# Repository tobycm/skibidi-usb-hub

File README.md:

# skibidi usb hub - 7-port usb hub with some ethernet and an audio out jack

me when my ethernet port and audio jack is broken and i need more usb A ports :bonk:

features:
 - 1 USB C port for upstream
 - 2 USB C ports
 - 2 USB A ports
 - 2 100M capable Ethernet ports
 - 1 Audio Jack (maybe both line in and line out)

## Build

JLCPCB Params:
- Stack up: JLC04161H-7628

## Pictures:

PCB Front: 

PCB Back:

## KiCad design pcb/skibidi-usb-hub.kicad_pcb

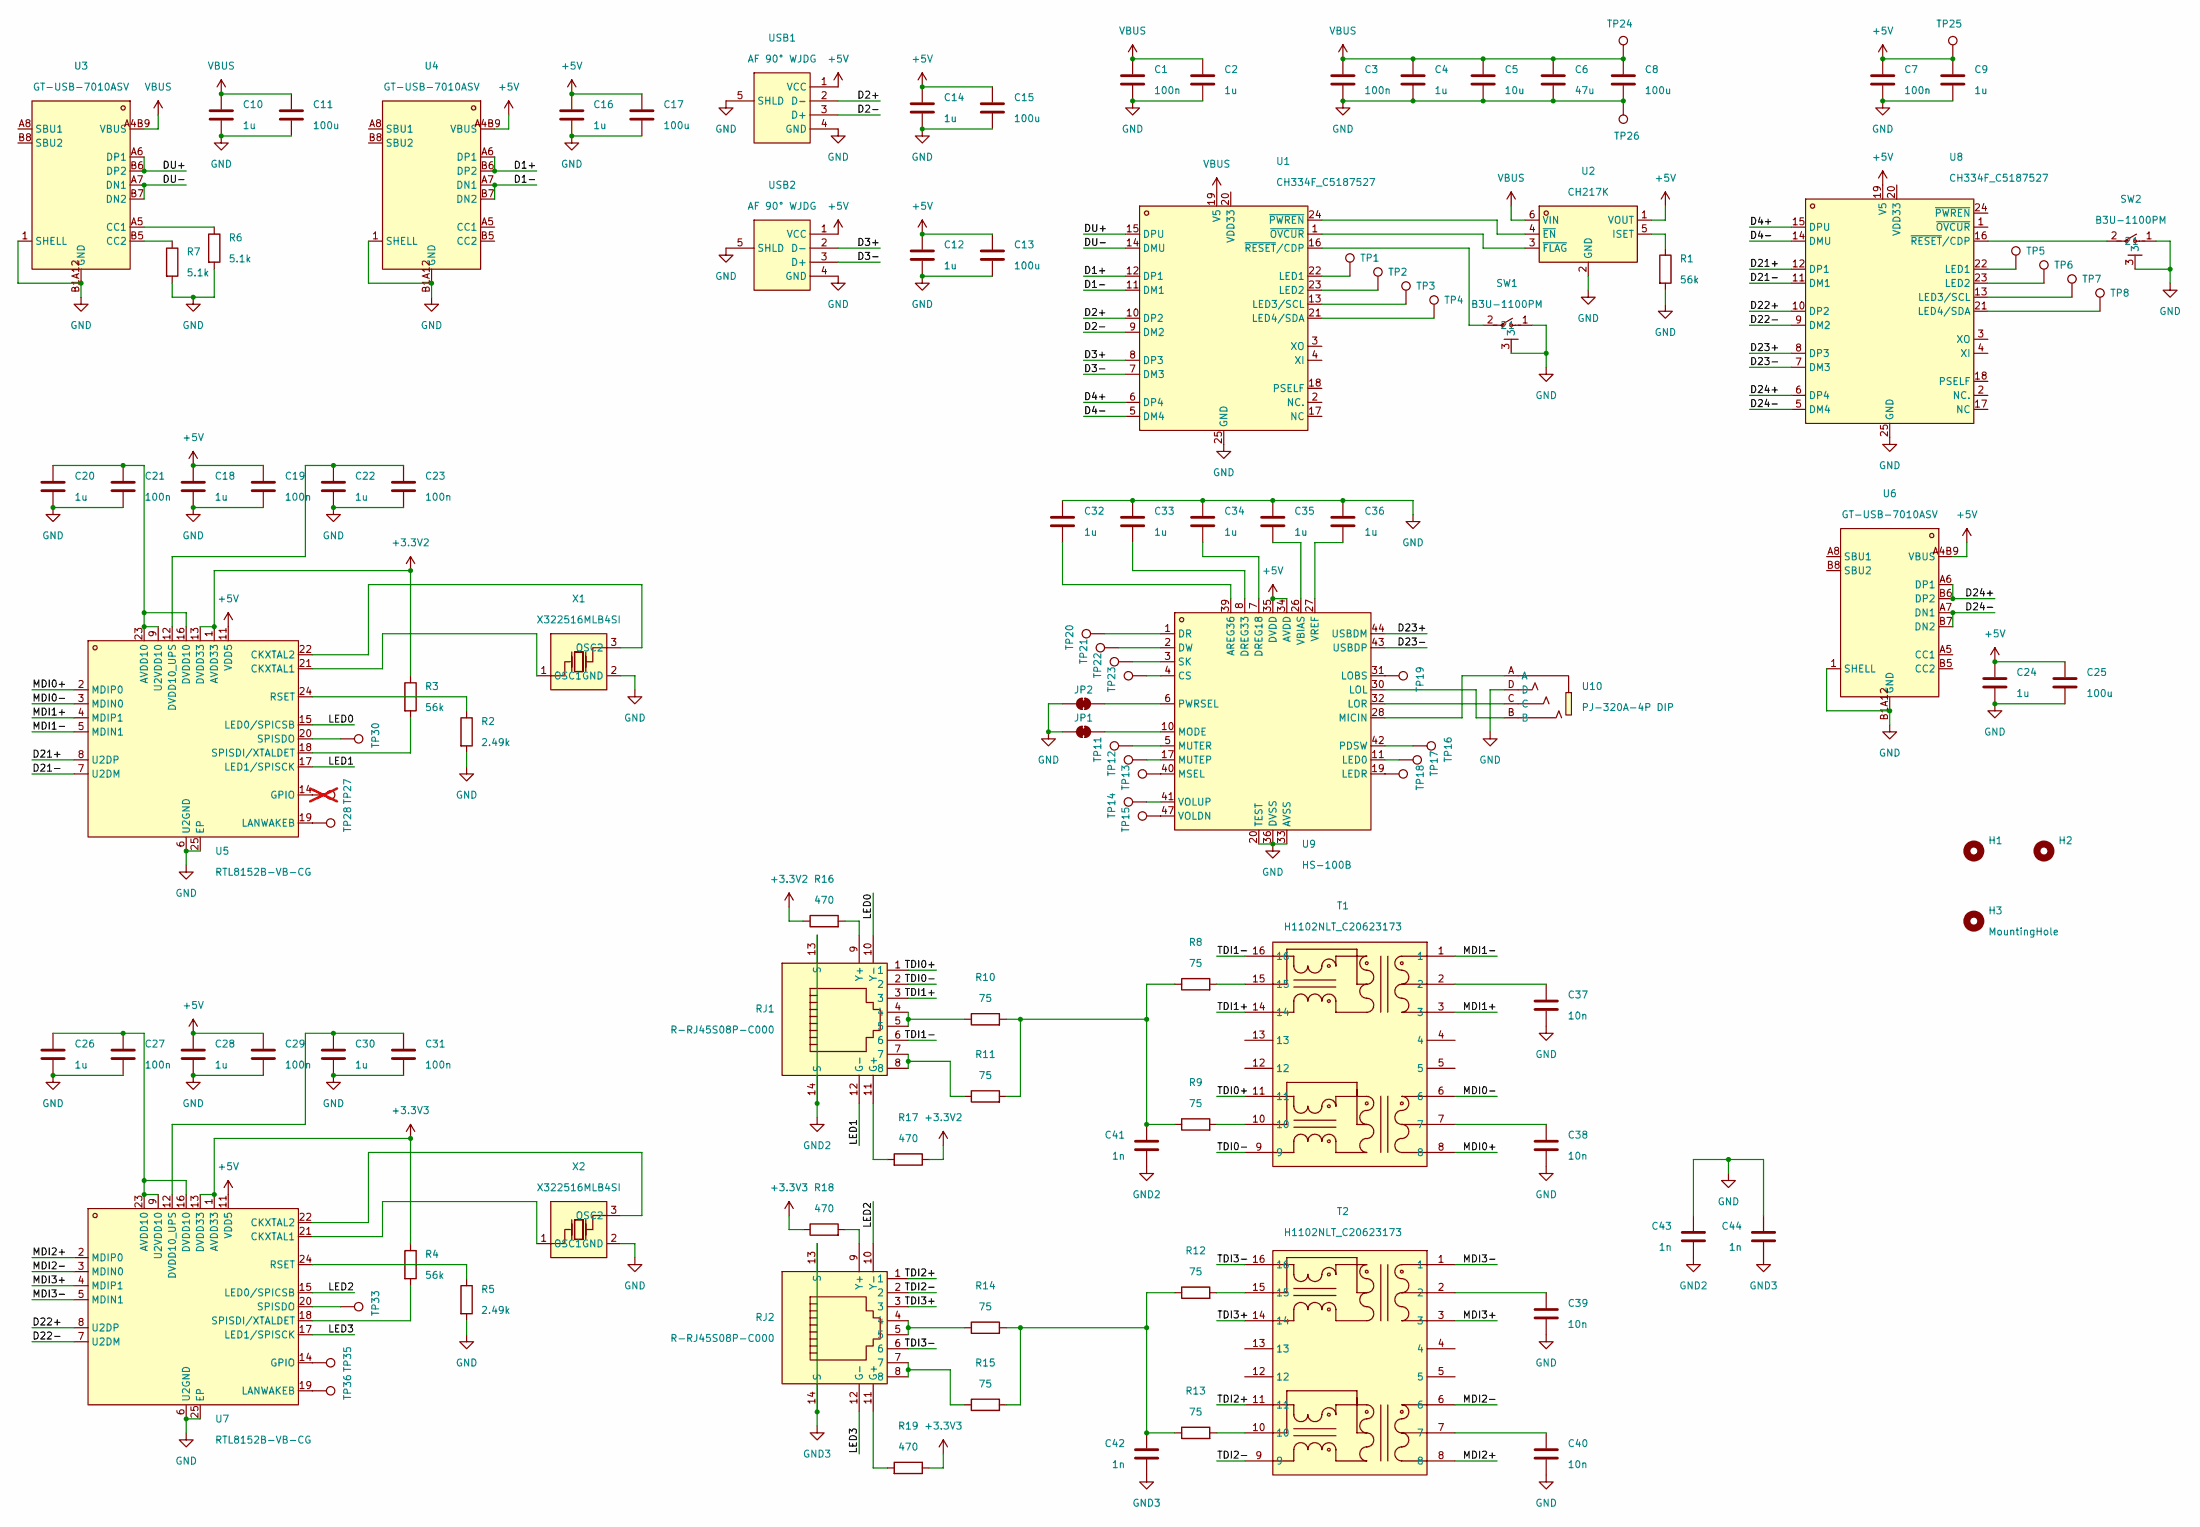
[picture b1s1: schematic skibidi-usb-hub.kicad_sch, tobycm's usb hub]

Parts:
C1, C3, C7, C19, C21, C23, C27, C29, C31: 100n; C_0402_1005Metric; LCSC Part # C1525
C2, C4, C9, C10, C12, C14, C16, C18, C20, C22, C24, C26, C28, C30, C32, C33, C34, C35, C36: 1u; C_0402_1005Metric; LCSC Part # C52923
C5: 10u; C_0603_1608Metric; LCSC Part # C19702
C6: 47u; C_0805_2012Metric; LCSC Part # C16780
C8, C11, C13, C15, C17, C25: 100u; C_1206_3216Metric; LCSC Part # C15008
C37, C38, C39, C40: 10n; C_0402_1005Metric; LCSC Part # C60133
C41, C42, C43, C44: 1n; C_1206_3216Metric; LCSC Part # C9196
H1, H2, H3: MountingHole; MountingHole_3.2mm_M3_Pad
JP1, JP2: SolderJumper_2_Bridged; SolderJumper-2_P1.3mm_Bridged_RoundedPad1.0x1.5mm
R1, R3, R4: 56k; R_0402_1005Metric; LCSC Part # C25796
R2, R5: 2.49k; R_0402_1005Metric; LCSC Part # C25884
R6, R7: 5.1k; R_0402_1005Metric; LCSC Part # C25905
R8, R9, R10, R11, R12, R13, R14, R15: 75; R_0402_1005Metric; LCSC Part # C114757
R16, R17, R18, R19: 470; R_0402_1005Metric; LCSC Part # C114877
RJ1, RJ2: R-RJ45S08P-C000; RJ45-TH_R-RJ45S08P-C000; LCSC Part C386764
SW1, SW2: B3U-1100PM; SW-SMD_3P-L3.0-W2.5-LS4.0; LCSC Part C6467298
T1, T2: H1102NLT_C20623173; XFMR-SMD_H1102NLT; LCSC Part C20623173
TP1, TP2, TP3, TP4, TP5, TP6, TP7, TP8, TP11, TP12, TP13, TP14, TP15, TP16, TP17, TP18, TP19, TP20, TP21, TP22, TP23, TP24, TP25, TP26, TP28, TP30, TP33, TP35, TP36: TestPoint; TestPoint_Pad_D1.0mm
TP27: TestPoint; TestPoint_Pad_D1.0mm; not fitted
U1, U8: CH334F_C5187527; QFN-24_L4.0-W4.0-P0.50-BL-EP2.8; LCSC Part C5187527
U2: CH217K; SOT-23-6_L2.9-W1.6-P0.95-LS2.8-BL; LCSC Part C7462749
U3, U4, U6: GT-USB-7010ASV; USB-C-SMD_G-SWITCH_GT-USB-7010ASV; LCSC Part C2988369
U5, U7: RTL8152B-VB-CG; QFN-24_L4.0-W4.0-P0.50-BL-EP2.0; LCSC Part C50656
U9: HS-100B; LQFP-48_L7.0-W7.0-P0.50-LS9.0-BL; LCSC Part C371351
U10: PJ-320A-4P DIP; AUDIO-TH_PJ-320A-4P-DIP; LCSC Part C18185602
USB1, USB2: AF 90° WJDG; USB-A-TH_AF-WJDG; LCSC Part C456018
X1, X2: X322516MLB4SI; OSC-SMD_4P-L3.2-W2.5-BL; LCSC Part C13738

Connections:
+3.3V2: R3.1, R16.1, R17.1, U5.1 (AVDD33), U5.10 (AVDD33), U5.13 (DVDD33)
+3.3V3: R4.1, R18.1, R19.1, U7.1 (AVDD33), U7.10 (AVDD33), U7.13 (DVDD33)
+5V: C7.1, C9.1, C12.1, C13.1, C14.1, C15.1, C16.1, C17.1, C18.1, C19.1, C24.1, C25.1, C28.1, C29.1, TP25.1, U2.1 (VOUT), U4.A4B9 (VBUS), U4.B4A9 (VBUS), U5.11 (VDD5), U6.A4B9 (VBUS), U6.B4A9 (VBUS), U7.11 (VDD5), U8.19 (V5), U9.29 (AVDD), U9.34 (AVDD), U9.35 (DVDD), USB1.1 (VCC), USB2.1 (VCC)
/D1+: U1.12 (DP1), U4.A6 (DP1), U4.B6 (DP2)
/D1-: U1.11 (DM1), U4.A7 (DN1), U4.B7 (DN2)
/D2+: U1.10 (DP2), USB1.2 (D-)
/D2-: U1.9 (DM2), USB1.3 (D+)
/D3+: U1.8 (DP3), USB2.2 (D-)
/D3-: U1.7 (DM3), USB2.3 (D+)
/D4+: U1.6 (DP4), U8.15 (DPU)
/D4-: U1.5 (DM4), U8.14 (DMU)
/D21+: U5.8 (U2DP), U8.12 (DP1)
/D21-: U5.7 (U2DM), U8.11 (DM1)
/D22+: U7.8 (U2DP), U8.10 (DP2)
/D22-: U7.7 (U2DM), U8.9 (DM2)
/D23+: U8.8 (DP3), U9.44 (USBDM)
/D23-: U8.7 (DM3), U9.43 (USBDP)
/D24+: U6.A6 (DP1), U6.B6 (DP2), U8.6 (DP4)
/D24-: U6.A7 (DN1), U6.B7 (DN2), U8.5 (DM4)
/DU+: U1.15 (DPU), U3.A6 (DP1), U3.B6 (DP2)
/DU-: U1.14 (DMU), U3.A7 (DN1), U3.B7 (DN2)
/LED0: RJ1.10 (Y-), U5.15 (LED0/SPICSB)
/LED1: RJ1.12 (G-), U5.17 (LED1/SPISCK)
/LED2: RJ2.10 (Y-), U7.15 (LED0/SPICSB)
/LED3: RJ2.12 (G-), U7.17 (LED1/SPISCK)
/MDI0+: T1.8, U5.2 (MDIP0)
/MDI0-: T1.6, U5.3 (MDIN0)
/MDI1+: T1.3, U5.4 (MDIP1)
/MDI1-: T1.1, U5.5 (MDIN1)
/MDI2+: T2.8, U7.2 (MDIP0)
/MDI2-: T2.6, U7.3 (MDIN0)
/MDI3+: T2.3, U7.4 (MDIP1)
/MDI3-: T2.1, U7.5 (MDIN1)
/TDI0+: RJ1.1, T1.11
/TDI0-: RJ1.2, T1.9
/TDI1+: RJ1.3, T1.14
/TDI1-: RJ1.6, T1.16
/TDI2+: RJ2.1, T2.11
/TDI2-: RJ2.2, T2.9
/TDI3+: RJ2.3, T2.14
/TDI3-: RJ2.6, T2.16
GND: C1.2, C2.2, C3.2, C4.2, C5.2, C6.2, C7.2, C8.2, C9.2, C10.2, C11.2, C12.2, C13.2, C14.2, C15.2, C16.2, C17.2, C18.2, C19.2, C20.2, C21.2, C22.2, C23.2, C24.2, C25.2, C26.2, C27.2, C28.2, C29.2, C30.2, C31.2, C32.1, C33.1, C34.1, C35.1, C36.1, C37.2, C38.2, C39.2, C40.2, C43.1, C44.1, JP1.1 (A), JP2.1 (A), R1.2, R2.2, R5.2, R6.2, R7.2, SW1.1, SW1.3, SW2.1, SW2.3, TP26.1, U1.25 (GND), U2.2 (GND), U3.1 (SHELL), U3.2 (SHELL), U3.3 (SHELL), U3.4 (SHELL), U3.A1B12 (GND), U3.B1A12 (GND), U4.1 (SHELL), U4.2 (SHELL), U4.3 (SHELL), U4.4 (SHELL), U4.A1B12 (GND), U4.B1A12 (GND), U5.6 (U2GND), U5.25 (EP), U6.1 (SHELL), U6.2 (SHELL), U6.3 (SHELL), U6.4 (SHELL), U6.A1B12 (GND), U6.B1A12 (GND), U7.6 (U2GND), U7.25 (EP), U8.25 (GND), U9.12 (DVSS), U9.20 (TEST), U9.25 (AVSS), U9.33 (AVSS), U9.36 (DVSS), U10.D, USB1.4 (GND), USB1.5 (SHLD), USB2.4 (GND), USB2.5 (SHLD), X1.2 (GND), X1.4 (GND), X2.2 (GND), X2.4 (GND)
GND2: C41.2, C43.2, RJ1.13 (S), RJ1.14 (S)
GND3: C42.2, C44.2, RJ2.13 (S), RJ2.14 (S)
unnamed: C37.1, T1.2
unnamed: C38.1, T1.7
unnamed: C39.1, T2.2
unnamed: C40.1, T2.7
unnamed: C41.1, R8.1, R9.1, R10.2, R11.2
unnamed: C42.1, R12.1, R13.1, R14.2, R15.2
unnamed: JP1.2 (B), U9.10 (MODE)
unnamed: JP2.2 (B), U9.6 (PWRSEL)
unnamed: R8.2, T1.15
unnamed: R9.2, T1.10
unnamed: R10.1, RJ1.4, RJ1.5
unnamed: R11.1, RJ1.7, RJ1.8
unnamed: R12.2, T2.15
unnamed: R13.2, T2.10
unnamed: R14.1, RJ2.4, RJ2.5
unnamed: R15.1, RJ2.7, RJ2.8
unnamed: R17.2, RJ1.11 (G+)
unnamed: R16.2, RJ1.9 (Y+)
unnamed: R19.2, RJ2.11 (G+)
unnamed: R18.2, RJ2.9 (Y+)
unnamed: TP1.1, U1.22 (LED1)
unnamed: TP2.1, U1.23 (LED2)
unnamed: TP3.1, U1.13 (LED3/SCL)
unnamed: TP4.1, U1.21 (LED4/SDA)
unnamed: U1.1 (~OVCUR), U2.3 (~FLAG)
unnamed: U1.24 (~PWREN), U2.4 (~EN)
unnamed: SW1.2, U1.16 (~RESET/CDP)
unnamed: R1.1, U2.5 (ISET)
unnamed: R6.1, U3.A5 (CC1)
unnamed: R7.1, U3.B5 (CC2)
unnamed: C20.1, C21.1, U5.9 (U2VDD10), U5.16 (DVDD10), U5.23 (AVDD10)
unnamed: U5.21 (CKXTAL1), X1.1 (OSC1)
unnamed: U5.22 (CKXTAL2), X1.3 (OSC2)
unnamed: C22.1, C23.1, U5.12 (DVDD10_UPS)
unnamed: TP27.1, U5.14 (GPIO)
unnamed: TP28.1, U5.19 (LANWAKEB)
unnamed: R2.1, U5.24 (RSET)
unnamed: R3.2, U5.18 (SPISDI/XTALDET)
unnamed: TP30.1, U5.20 (SPISDO)
unnamed: C26.1, C27.1, U7.9 (U2VDD10), U7.16 (DVDD10), U7.23 (AVDD10)
unnamed: U7.21 (CKXTAL1), X2.1 (OSC1)
unnamed: U7.22 (CKXTAL2), X2.3 (OSC2)
unnamed: C30.1, C31.1, U7.12 (DVDD10_UPS)
unnamed: TP35.1, U7.14 (GPIO)
unnamed: TP36.1, U7.19 (LANWAKEB)
unnamed: R5.1, U7.24 (RSET)
unnamed: R4.2, U7.18 (SPISDI/XTALDET)
unnamed: TP33.1, U7.20 (SPISDO)
unnamed: TP5.1, U8.22 (LED1)
unnamed: TP6.1, U8.23 (LED2)
unnamed: TP7.1, U8.13 (LED3/SCL)
unnamed: TP8.1, U8.21 (LED4/SDA)
unnamed: SW2.2, U8.16 (~RESET/CDP)
unnamed: C32.2, U9.39 (AREG36)
unnamed: TP23.1, U9.4 (CS)
unnamed: TP20.1, U9.1 (DR)
unnamed: C34.2, U9.7 (DREG18)
unnamed: C33.2, U9.8 (DREG33)
unnamed: TP21.1, U9.2 (DW)
unnamed: TP17.1, U9.11 (LED0)
unnamed: TP18.1, U9.19 (LEDR)
unnamed: TP19.1, U9.31 (LOBS)
unnamed: U9.30 (LOL), U10.B
unnamed: U9.32 (LOR), U10.C
unnamed: U9.28 (MICIN), U10.A
unnamed: TP13.1, U9.40 (MSEL)
unnamed: TP12.1, U9.17 (MUTEP)
unnamed: TP11.1, U9.5 (MUTER)
unnamed: TP16.1, U9.42 (PDSW)
unnamed: TP22.1, U9.3 (SK)
unnamed: C35.2, U9.26 (VBIAS)
unnamed: TP15.1, U9.47 (VOLDN)
unnamed: TP14.1, U9.41 (VOLUP)
unnamed: C36.2, U9.27 (VREF)
VBUS: C1.1, C2.1, C3.1, C4.1, C5.1, C6.1, C8.1, C10.1, C11.1, TP24.1, U1.19 (V5), U2.6 (VIN), U3.A4B9 (VBUS), U3.B4A9 (VBUS)

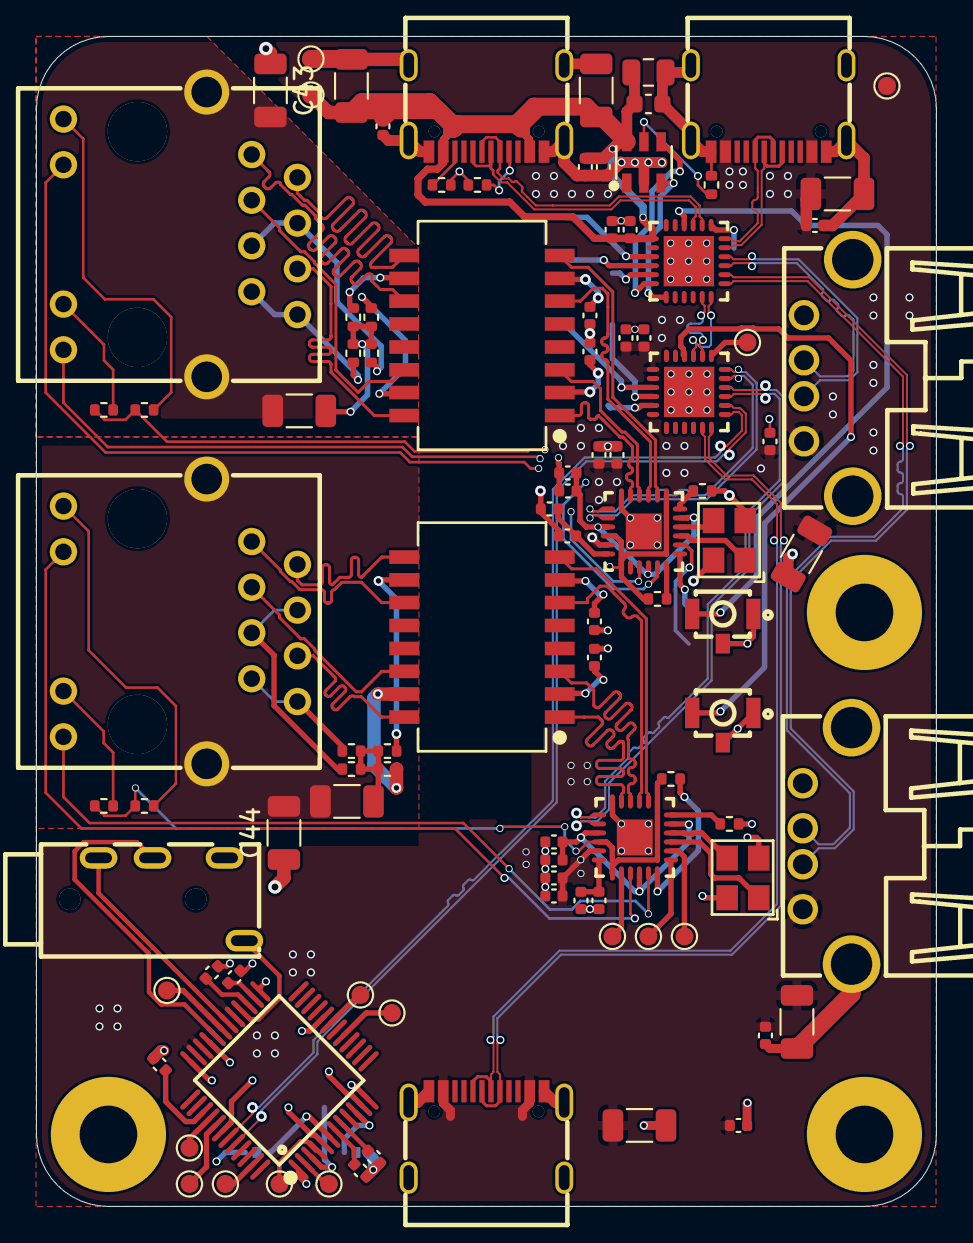
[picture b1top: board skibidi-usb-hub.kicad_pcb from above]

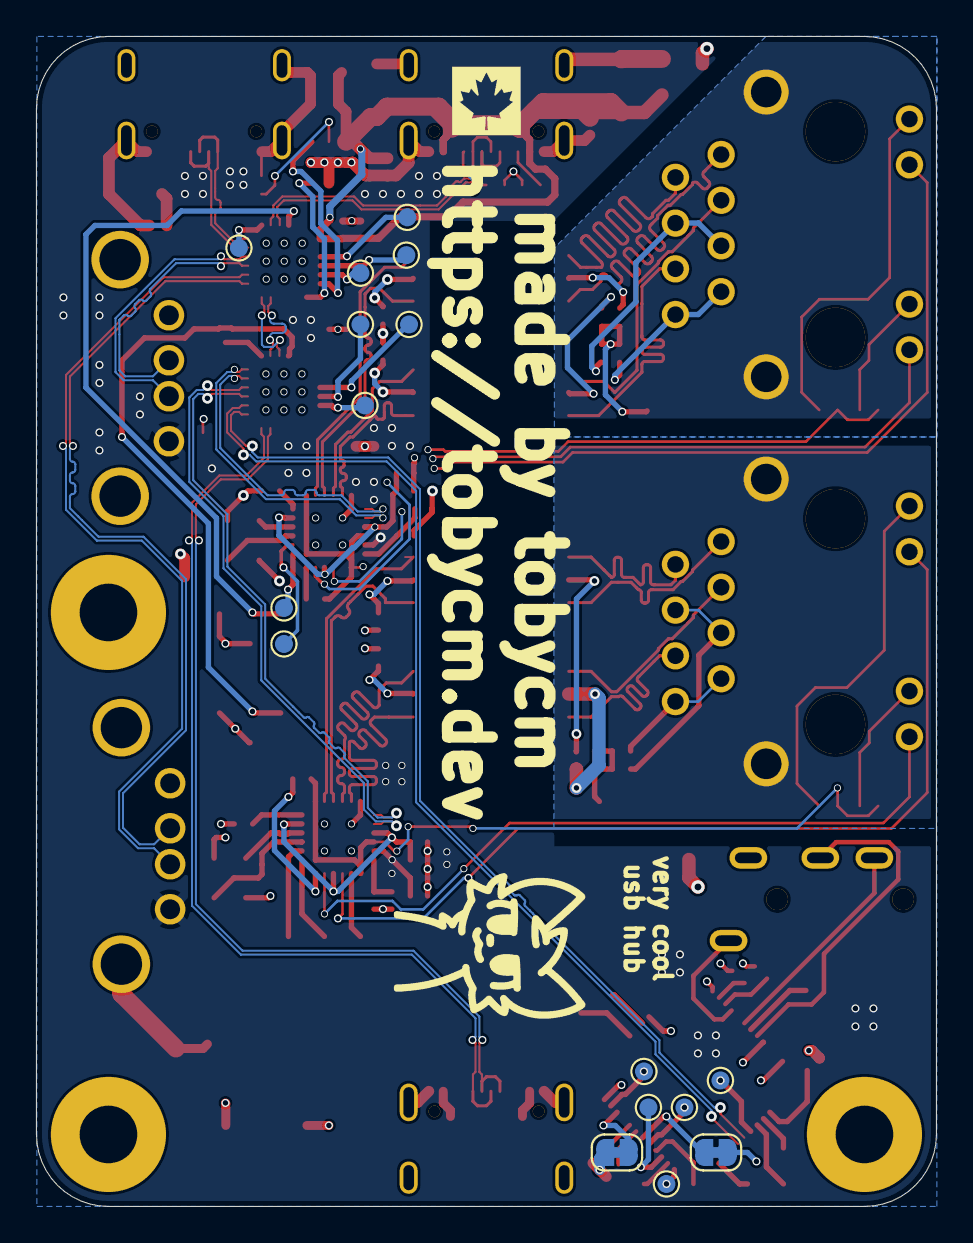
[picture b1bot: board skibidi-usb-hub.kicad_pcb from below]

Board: 4 copper layers, 50.0 x 65.0 mm, 117 parts (16 on the bottom side), 118 nets.

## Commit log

2025-09-20 init kicad
2025-09-21 finished schematic siuuuuu
2025-10-25 PCB done!!!
2025-10-26 add bom, update src, add readme
2025-10-26 update and add pcb step
2025-11-01 add EMI capacitor for ethernet chassis ground and logic ground
2025-11-01 update bom without PCBA
